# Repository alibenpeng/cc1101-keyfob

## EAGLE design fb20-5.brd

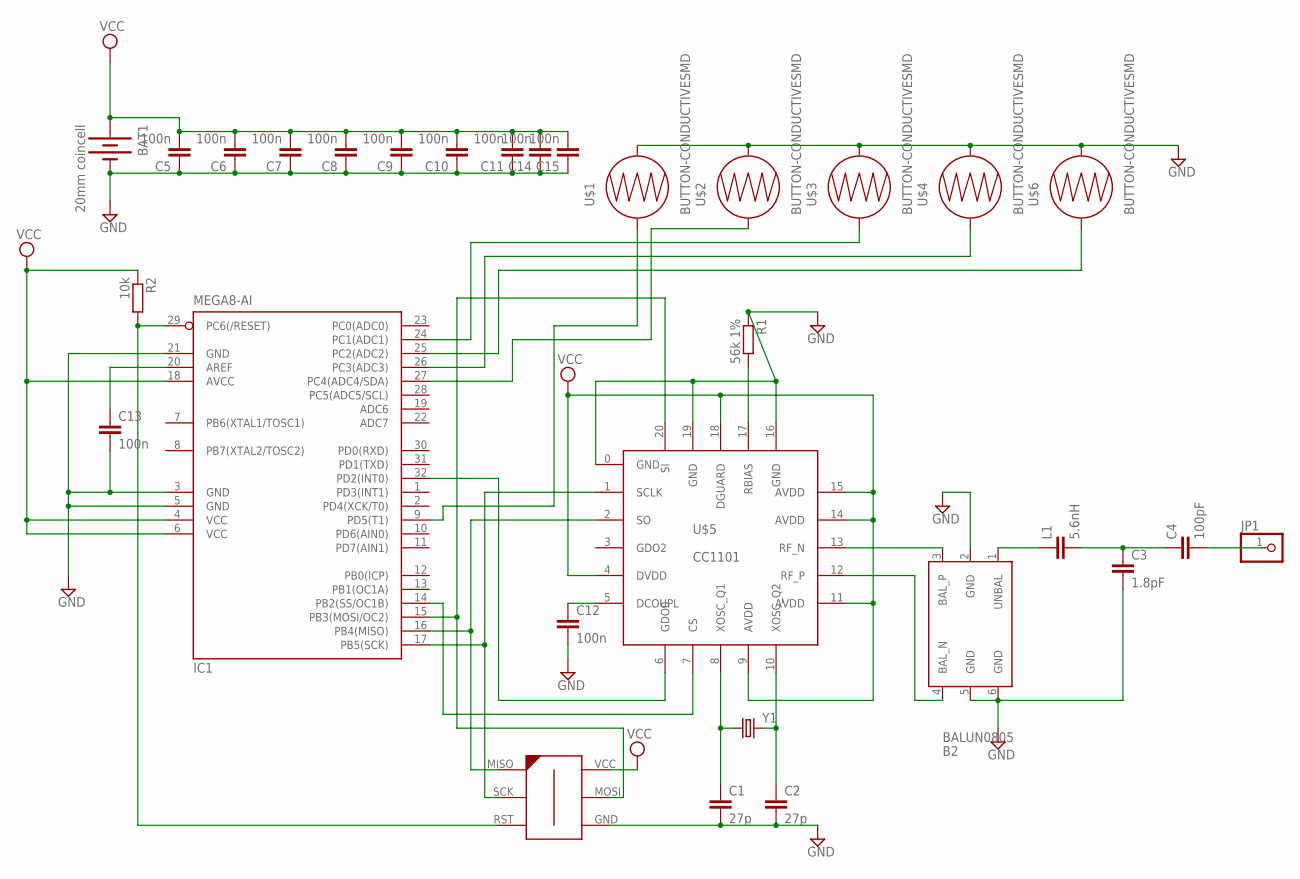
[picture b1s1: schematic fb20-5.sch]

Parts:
B2: BALUN0805; BALUN
BAT1: 20mm coincell; BATTCON_20MM_4LEGS
C1, C2: 27p; C0402
C3: 1.8pF; C0402
C4: 100pF; C0402
C5, C6, C7, C8, C9, C10, C11, C12, C13, C14, C15: 100n; C0402
IC1: MEGA8-AI; TQFP32-08
JP1: PINHD-1X1; 1X01
L1: 5.6nH; C0603
R1: 56k 1%; R0402
R2: 10k; R0402
U$1, U$2, U$3, U$4, U$6: BUTTON-CONDUCTIVESMD; BUTTON-CONDUCTIVE
U$5: CC1101; QFN20
U$7: AVR-ISP-6-EDGE; 6PAD_ISP
Y1: CRYSTAL5X3; CRYSTAL-SMD-5X3

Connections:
GND: B2.2 (GND), B2.5 (GND), B2.6 (GND), BAT1.2 (-), C1.2, C2.2, C3.2, C5.1, C6.1, C7.1, C8.1, C9.1, C10.1, C11.1, C12.2, C13.2, C14.1, C15.1, IC1.3 (GND), IC1.5 (GND), IC1.21 (GND), R1.1, U$1.2, U$2.2, U$3.2, U$4.2, U$5.0 (GND), U$5.16 (GND), U$5.19 (GND), U$6.2, U$7.GND
unnamed: B2.3 (BAL_P), U$5.13 (RF_N)
unnamed: B2.4 (BAL_N), U$5.12 (RF_P)
unnamed: C1.1, U$5.8 (XOSC_Q1), Y1.1
unnamed: C2.1, U$5.10 (XOSC_Q2), Y1.3 (2)
unnamed: IC1.17 (PB5(SCK)), U$5.1 (SCLK), U$7.SCK
unnamed: IC1.14 (PB2(SS/OC1B)), U$5.7 (CS)
unnamed: IC1.29 (PC6(/RESET)), R2.2, U$7.RST
unnamed: IC1.32 (PD2(INT0)), U$5.6 (GDO0)
unnamed: B2.1 (UNBAL), L1.1
unnamed: C3.1, C4.1, L1.2
unnamed: R1.2, U$5.17 (RBIAS)
unnamed: IC1.16 (PB4(MISO)), U$5.2 (SO), U$7.MISO
unnamed: IC1.15 (PB3(MOSI/OC2)), U$5.20 (SI), U$7.MOSI
unnamed: C12.1, U$5.5 (DCOUPL)
unnamed: C13.1, IC1.20 (AREF)
unnamed: IC1.9 (PD5(T1)), U$1.1
unnamed: IC1.27 (PC4(ADC4/SDA)), U$2.1
unnamed: IC1.24 (PC1(ADC1)), U$3.1
unnamed: IC1.26 (PC3(ADC3)), U$4.1
unnamed: C4.2, JP1.1
unnamed: IC1.25 (PC2(ADC2)), U$6.1
VCC: BAT1.1 (+), C5.2, C6.2, C7.2, C8.2, C9.2, C10.2, C11.2, C14.2, C15.2, IC1.4 (VCC), IC1.6 (VCC), IC1.18 (AVCC), R2.1, U$5.4 (DVDD), U$5.9 (AVDD), U$5.11 (AVDD), U$5.14 (AVDD), U$5.15 (AVDD), U$5.18 (DGUARD), U$7.VCC

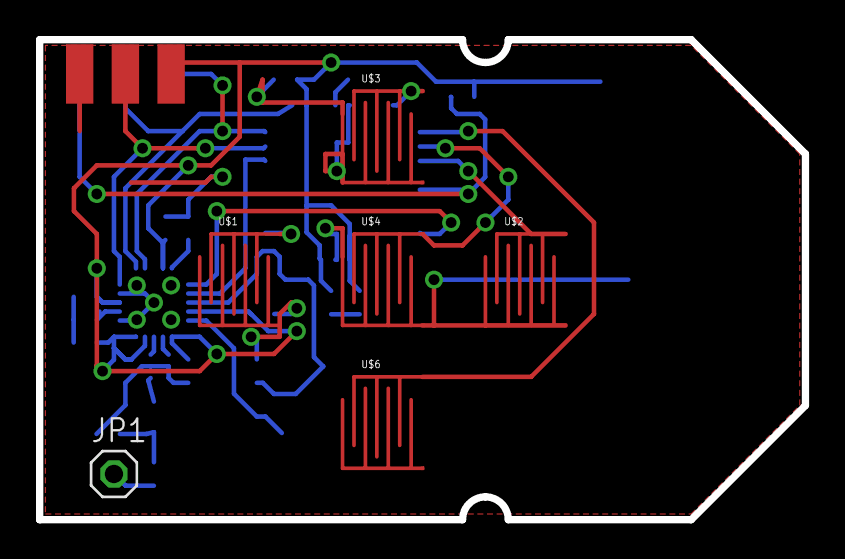
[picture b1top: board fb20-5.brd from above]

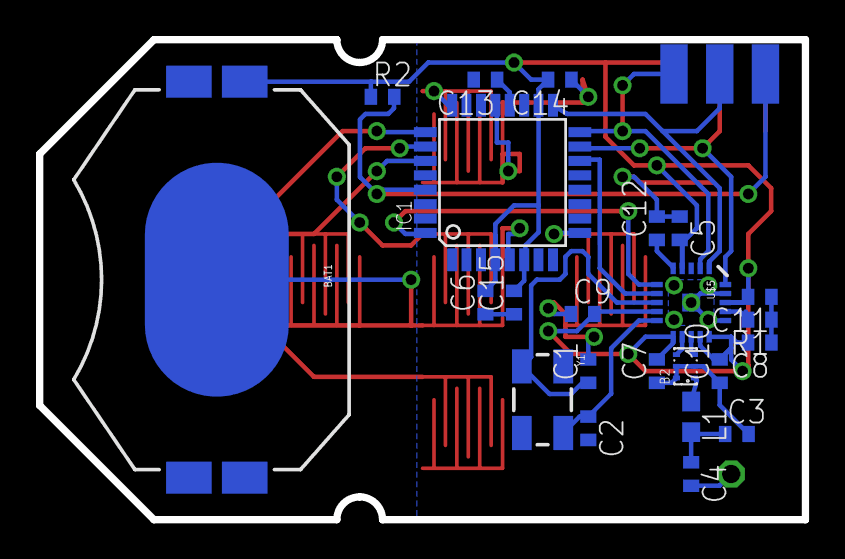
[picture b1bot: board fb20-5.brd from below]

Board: 2 copper layers, 42.5 x 26.7 mm, 30 parts (24 on the bottom side), 23 nets.

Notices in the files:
parts and their libraries:
SparkFun-FreqCtrl: Licensing: CC v3.0 Share-Alike You are welcome to use this library for commercial purposes.
